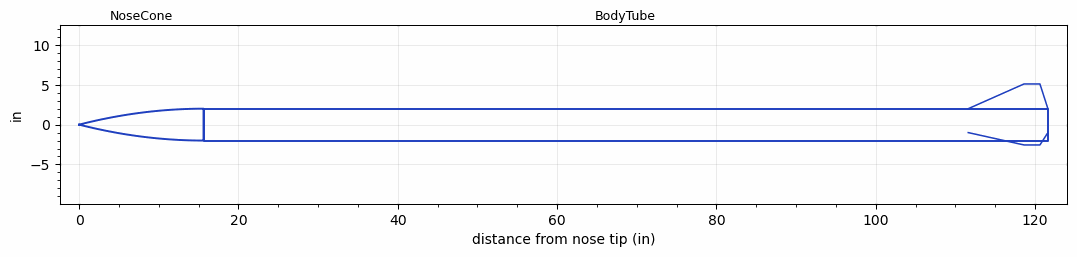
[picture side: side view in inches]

<RASAeroDocument>
 <FileVersion>2</FileVersion>
 <RocketDesign>
  <NoseCone>
   <Length>15.616</Length>
   <Diameter>4</Diameter>
   <Shape>Parabolic</Shape>
   <BluntRadius>0.1</BluntRadius>
   <Location>0</Location>
  </NoseCone>
  <BodyTube>
   <Length>106</Length>
   <Diameter>4</Diameter>
   <Location>15.616</Location>
   <Fin>
    <Count>3</Count>
    <Chord>10</Chord>
    <Span>3.105</Span>
    <SweepDistance>7</SweepDistance>
    <TipChord>2</TipChord>
    <Thickness>0.25</Thickness>
    <LERadius>0.125</LERadius>
    <Location>10</Location>
    <AirfoilSection>Double Wedge</AirfoilSection>
    <FX1>1</FX1>
   </Fin>
  </BodyTube>
  <Surface>Galvanized Metal</Surface>
  <ModifiedBarrowman>False</ModifiedBarrowman>
  <Turbulence>False</Turbulence>
  <UseBooster1>False</UseBooster1>
  <UseBooster2>False</UseBooster2>
 </RocketDesign>
 <LaunchSite>
  <Altitude>5000</Altitude>
  <Pressure>0</Pressure>
  <RodAngle>7</RodAngle>
  <RodLength>18</RodLength>
  <Temperature>95</Temperature>
  <WindSpeed>30</WindSpeed>
 </LaunchSite>
 <Recovery>
  <Altitude1>1000</Altitude1>
  <Altitude2>1500</Altitude2>
  <DeviceType1>Parachute</DeviceType1>
  <DeviceType2>Parachute</DeviceType2>
  <Event1>True</Event1>
  <Event2>True</Event2>
  <Size1>30.57</Size1>
  <Size2>96</Size2>
  <EventType1>Apogee</EventType1>
  <EventType2>Altitude</EventType2>
  <CD1>0.75</CD1>
  <CD2>2.2</CD2>
 </Recovery>
 <SimulationList>
  <Simulation>
   <SustainerEngine>N2000W  (AT)</SustainerEngine>
   <SustainerLaunchWt>55.5</SustainerLaunchWt>
   <SustainerNozzleDiameter>1.5</SustainerNozzleDiameter>
   <SustainerCG>71.5</SustainerCG>
   <SustainerIgnitionDelay>0</SustainerIgnitionDelay>
   <Booster1SeparationDelay>0</Booster1SeparationDelay>
   <Booster1IgnitionDelay>0</Booster1IgnitionDelay>
   <IncludeBooster1>False</IncludeBooster1>
   <Booster2Delay>0</Booster2Delay>
   <IncludeBooster2>False</IncludeBooster2>
   <TimetoApogee>43.14877</TimetoApogee>
   <MaxAltitude>31213.38</MaxAltitude>
   <MaxVelocity>1669.655</MaxVelocity>
  </Simulation>
  <Simulation>
   <SustainerEngine>N3300  (AT)</SustainerEngine>
   <SustainerLaunchWt>55</SustainerLaunchWt>
   <SustainerNozzleDiameter>2</SustainerNozzleDiameter>
   <SustainerCG>71.1</SustainerCG>
   <SustainerIgnitionDelay>0</SustainerIgnitionDelay>
   <Booster1SeparationDelay>0</Booster1SeparationDelay>
   <Booster1IgnitionDelay>0</Booster1IgnitionDelay>
   <IncludeBooster1>False</IncludeBooster1>
   <Booster2Delay>0</Booster2Delay>
   <IncludeBooster2>False</IncludeBooster2>
   <TimetoApogee>42.07895</TimetoApogee>
   <MaxAltitude>30924.41</MaxAltitude>
   <MaxVelocity>1874.421</MaxVelocity>
  </Simulation>
  <Simulation>
   <SustainerEngine>N2220DM  (AT)</SustainerEngine>
   <SustainerLaunchWt>55</SustainerLaunchWt>
   <SustainerNozzleDiameter>2</SustainerNozzleDiameter>
   <SustainerCG>71</SustainerCG>
   <SustainerIgnitionDelay>0</SustainerIgnitionDelay>
   <Booster1SeparationDelay>0</Booster1SeparationDelay>
   <Booster1IgnitionDelay>0</Booster1IgnitionDelay>
   <IncludeBooster1>False</IncludeBooster1>
   <Booster2Delay>0</Booster2Delay>
   <IncludeBooster2>False</IncludeBooster2>
   <TimetoApogee>37.30975</TimetoApogee>
   <MaxAltitude>23028.9</MaxAltitude>
   <MaxVelocity>1436.808</MaxVelocity>
  </Simulation>
  <Simulation>
   <SustainerEngine>N1000W  (AT)</SustainerEngine>
   <SustainerLaunchWt>56</SustainerLaunchWt>
   <SustainerNozzleDiameter>1.25</SustainerNozzleDiameter>
   <SustainerCG>72</SustainerCG>
   <SustainerIgnitionDelay>0</SustainerIgnitionDelay>
   <Booster1SeparationDelay>0</Booster1SeparationDelay>
   <Booster1IgnitionDelay>0</Booster1IgnitionDelay>
   <IncludeBooster1>False</IncludeBooster1>
   <Booster2Delay>0</Booster2Delay>
   <IncludeBooster2>False</IncludeBooster2>
   <TimetoApogee>41.89898</TimetoApogee>
   <MaxAltitude>26872.77</MaxAltitude>
   <MaxVelocity>1423.913</MaxVelocity>
  </Simulation>
 </SimulationList>
</RASAeroDocument>
